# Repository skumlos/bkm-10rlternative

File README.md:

BKM-10Rlternative, a plug-and-play replacement for the BKM-10R/11R (except for memory card, for now).

Inspired by Aaron Bonhams BKM-10Rduino, which is genious!

Still early, and there's a LOT of components, plus some tweaks might still be needed: 
* Button RC-filters, as I feel that the 10nF should be replaced with 100nF, but needs testing.
* LED current limiting resistors is of course a preference. I used 470 Ohm in my first prototype.
* UART CTS/RTS pins are sorta irrelevant, as they're set static anyways. Removing these would also free
up pins for porting to regular Atmega328P/Arduino Nano 3.0 board.
* The discrete SS pins for each MCP23S17 should be irrelevant when using multiple addresses (which they
are configured as) so removing them in the future, to free up pins would be an idea.

Plans on memory card stuff for firmware updates and such via SD cards, is planned, at least to be researched.

While the unit is modeled after the BKM-11R, the wiring of the serial port is done like the BKM-10R, meaning
it uses a straight through male-male RS232/DE-9 cable, just like the BKM-10R. It is therefore not compatible
with BKM-11R DE-9 -> mini-DIN cables, unless you make your own.

There is a "classic" IR receiver designed into the PCB. It is unused at the moment, and shouldn't be mounted
before the software actually uses it. It was/is meant to be able to replicate some of the BKM-10Rduino 
functionality at some point, to have an all-in-one unit.

(2022) Martin Hejnfelt, martin@hejnfelt.com

https://www.immerhax.com

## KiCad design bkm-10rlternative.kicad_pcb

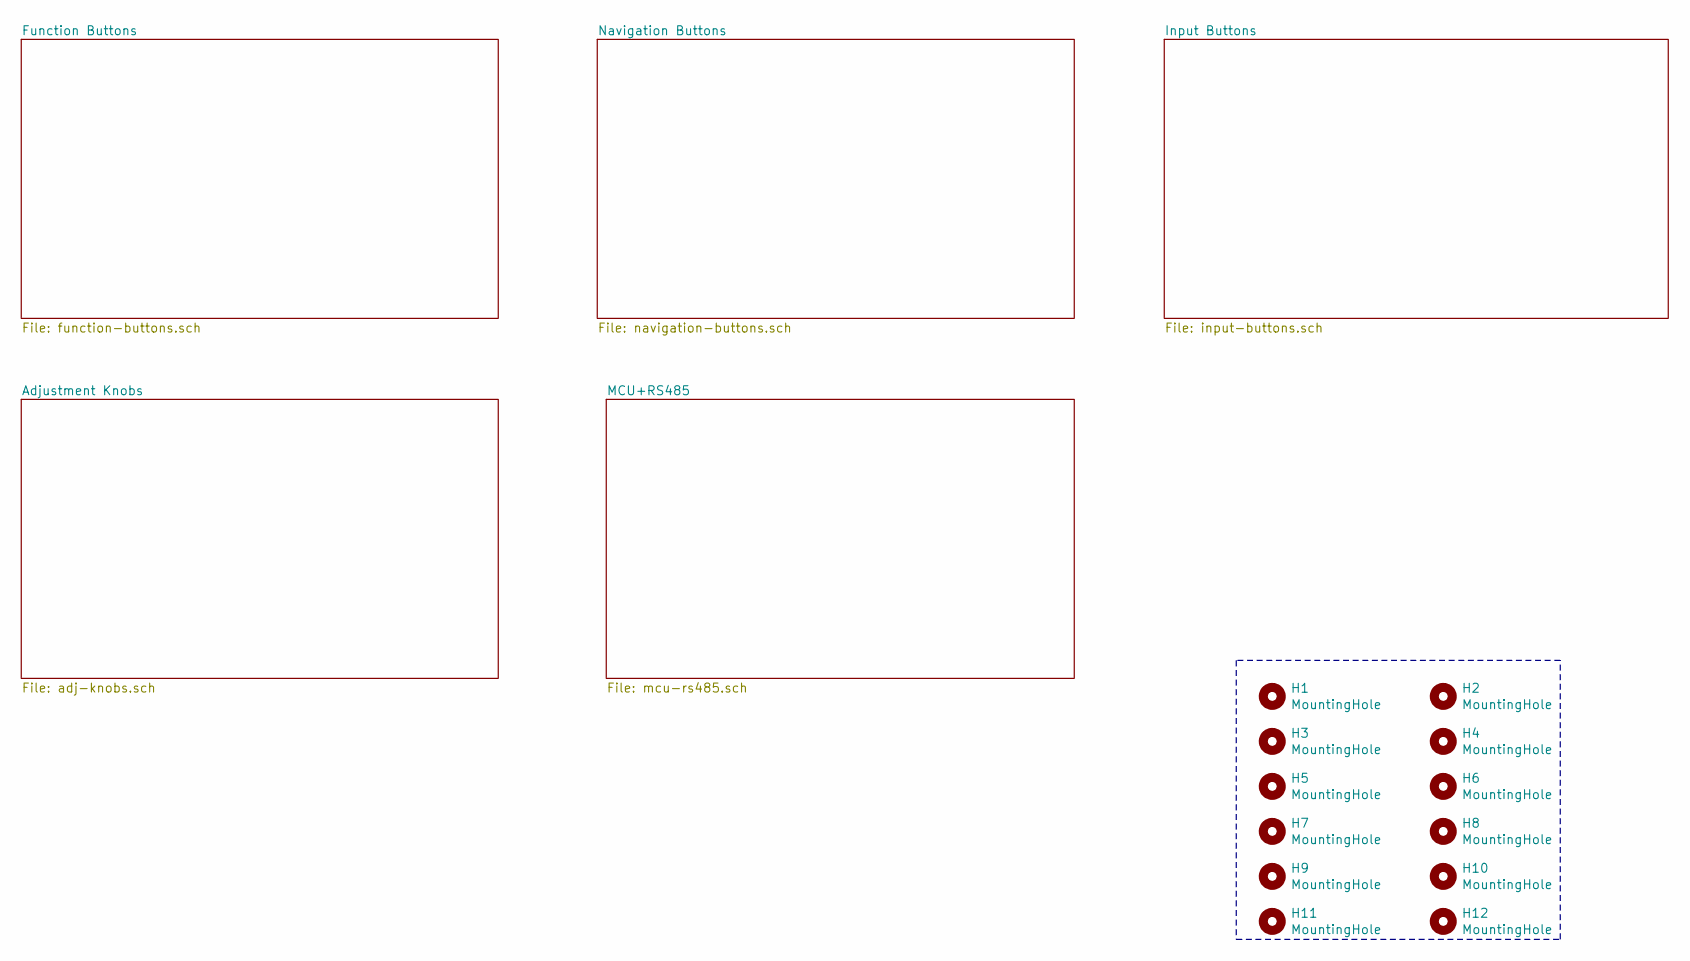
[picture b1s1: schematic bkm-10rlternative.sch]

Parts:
H1, H2, H3, H4, H5, H6, H7, H8, H9, H10, H11, H12: MountingHole; MountingHole_3.2mm_M3

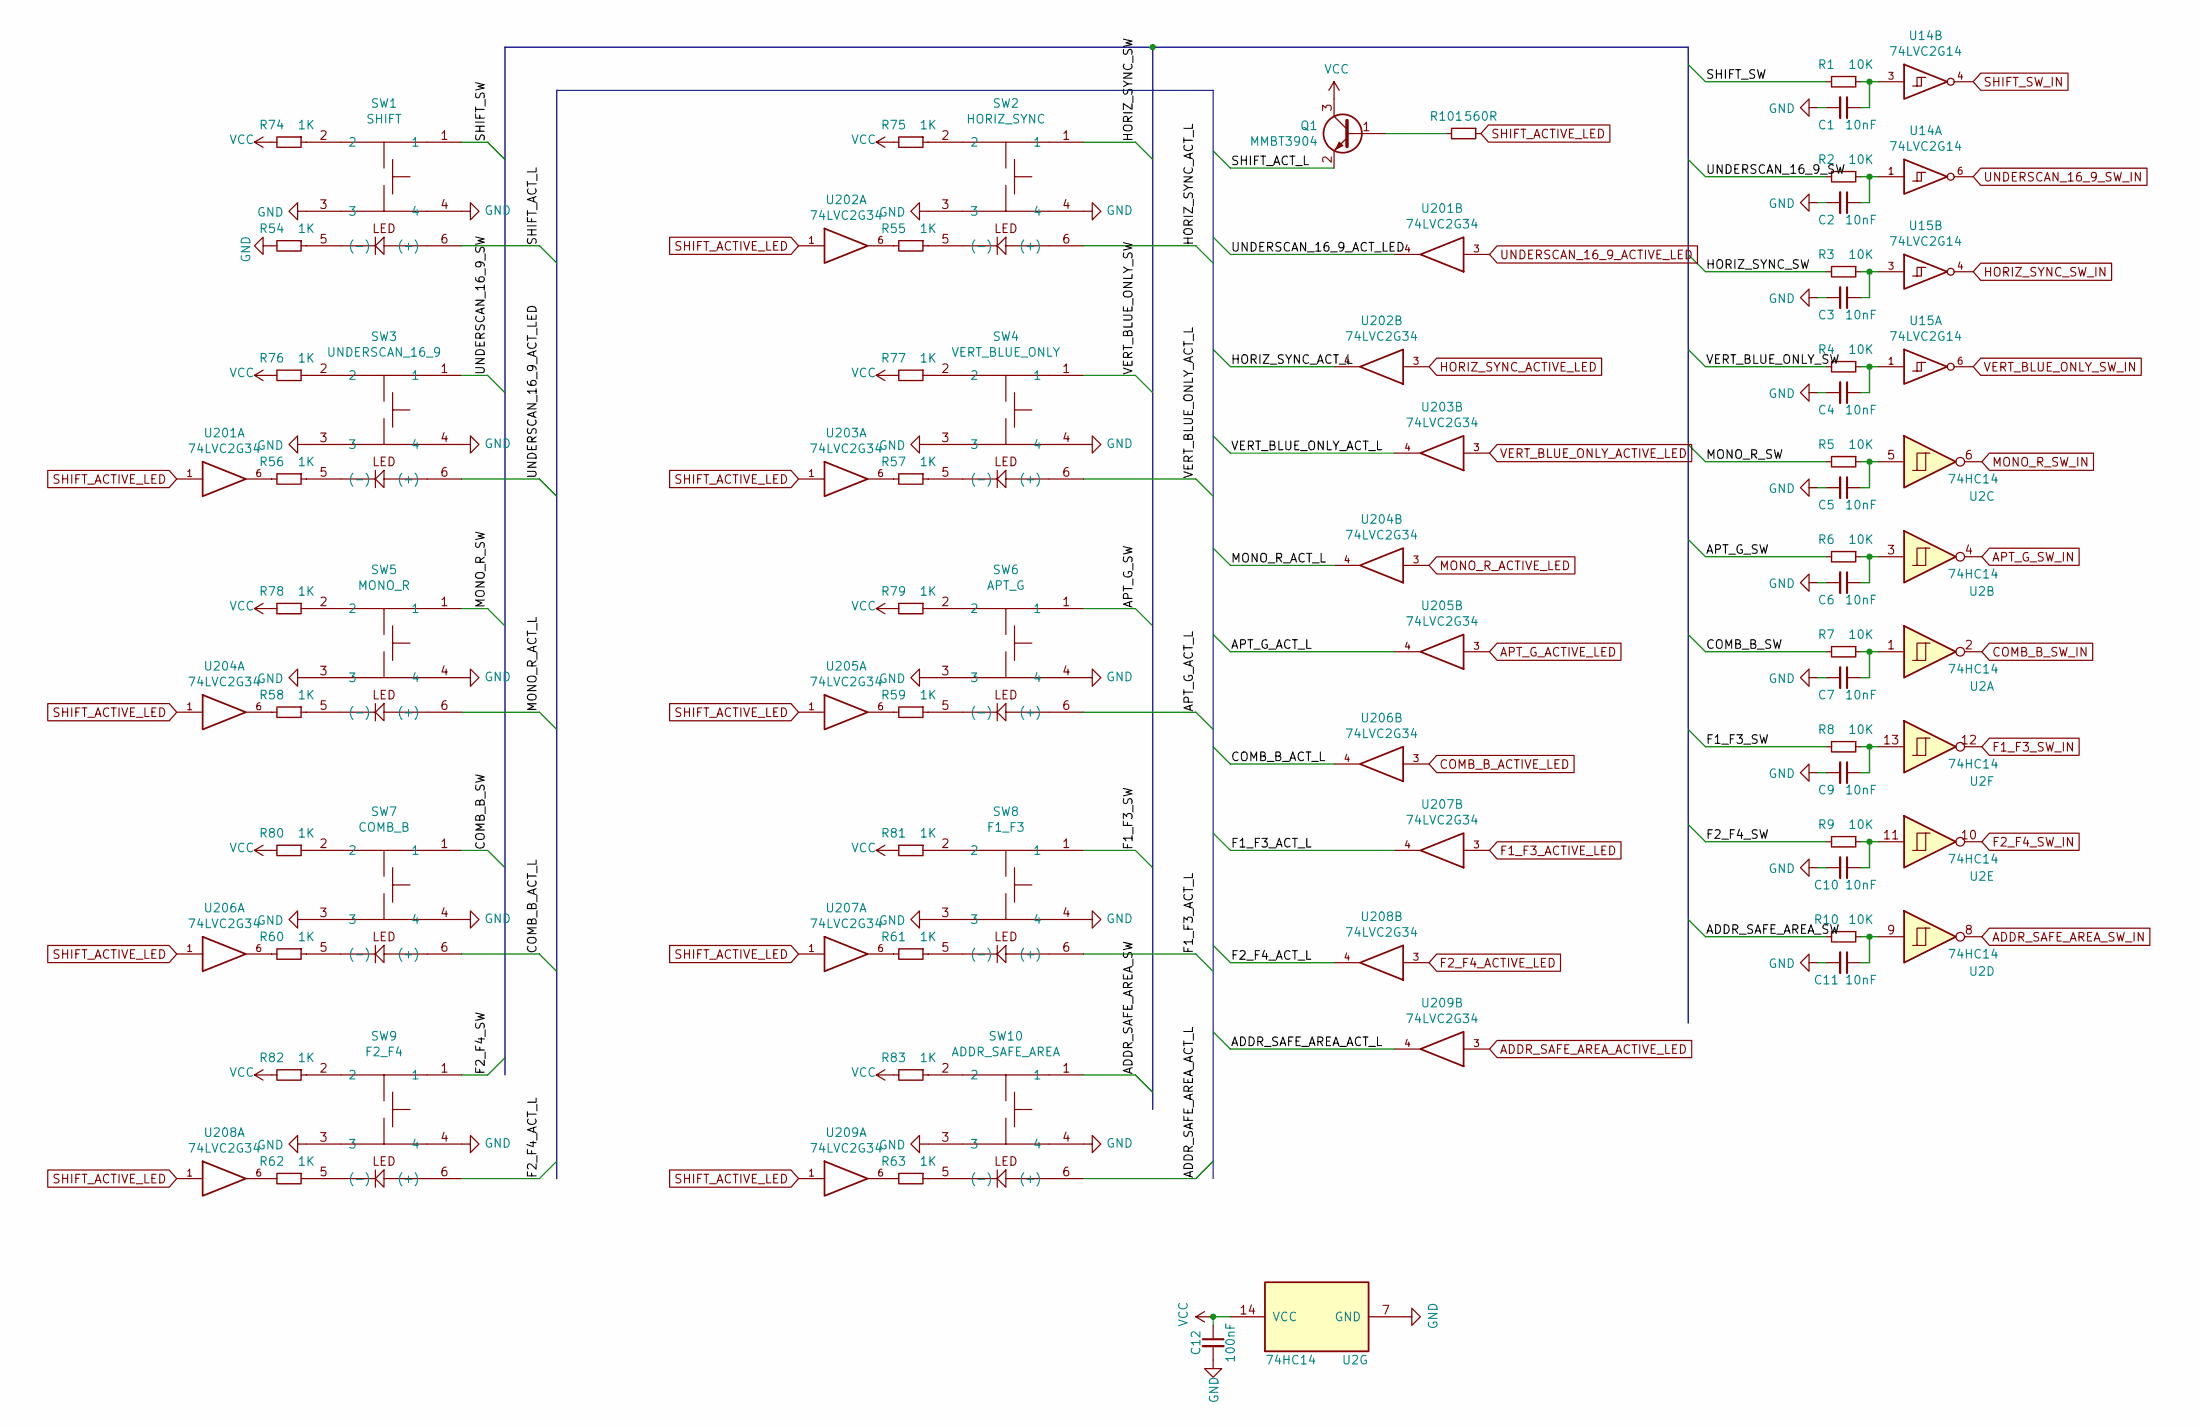
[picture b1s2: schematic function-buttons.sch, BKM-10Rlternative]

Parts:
C1, C2, C3, C4, C5, C6, C7, C9, C10, C11: 10nF; C_0603_1608Metric_Pad1.08x0.95mm_HandSolder
C12: 100nF; C_0603_1608Metric_Pad1.08x0.95mm_HandSolder
Q1: MMBT3904; SOT-23
R1, R2, R3, R4, R5, R6, R7, R8, R9, R10: 10K; R_0603_1608Metric_Pad0.98x0.95mm_HandSolder
R54, R55, R56, R57, R58, R59, R60, R61, R62, R63, R74, R75, R76, R77, R78, R79, R80, R81, R82, R83: 1K; R_0603_1608Metric_Pad0.98x0.95mm_HandSolder
R101: 560R; R_0603_1608Metric_Pad0.98x0.95mm_HandSolder
SW1: SHIFT; TL-1265
SW2: HORIZ_SYNC; TL-1265
SW3: UNDERSCAN_16_9; TL-1265
SW4: VERT_BLUE_ONLY; TL-1265
SW5: MONO_R; TL-1265
SW6: APT_G; TL-1265
SW7: COMB_B; TL-1265
SW8: F1_F3; TL-1265
SW9: F2_F4; TL-1265
SW10: ADDR_SAFE_AREA; TL-1265
U2: 74HC14; TSSOP-14_4.4x5mm_P0.65mm
U14, U15: 74LVC2G14; SOT-23-6_Handsoldering
U201, U202, U203, U204, U205, U206, U207, U208, U209: 74LVC2G34; SOT-23-6_Handsoldering

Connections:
/Function Buttons/ADDR_SAFE_AREA_ACT_L: SW10.6 ((+)), U209.4
/Function Buttons/ADDR_SAFE_AREA_SW: R10.2, SW10.1
/Function Buttons/APT_G_ACT_L: SW6.6 ((+)), U205.4
/Function Buttons/APT_G_SW: R6.2, SW6.1
/Function Buttons/COMB_B_ACT_L: SW7.6 ((+)), U206.4
/Function Buttons/COMB_B_SW: R7.2, SW7.1
/Function Buttons/F1_F3_ACT_L: SW8.6 ((+)), U207.4
/Function Buttons/F1_F3_SW: R8.2, SW8.1
/Function Buttons/F2_F4_ACT_L: SW9.6 ((+)), U208.4
/Function Buttons/F2_F4_SW: R9.2, SW9.1
/Function Buttons/HORIZ_SYNC_ACT_L: SW2.6 ((+)), U202.4
/Function Buttons/HORIZ_SYNC_SW: R3.2, SW2.1
/Function Buttons/MONO_R_ACT_L: SW5.6 ((+)), U204.4
/Function Buttons/MONO_R_SW: R5.2, SW5.1
/Function Buttons/SHIFT_ACT_L: Q1.2 (E), SW1.6 ((+))
/Function Buttons/SHIFT_SW: R1.2, SW1.1
/Function Buttons/UNDERSCAN_16_9_ACT_LED: SW3.6 ((+)), U201.4
/Function Buttons/UNDERSCAN_16_9_SW: R2.2, SW3.1
/Function Buttons/VERT_BLUE_ONLY_ACT_L: SW4.6 ((+)), U203.4
/Function Buttons/VERT_BLUE_ONLY_SW: R4.2, SW4.1
ADDR_SAFE_AREA_ACTIVE_LED: U209.3; also elsewhere on the board
ADDR_SAFE_AREA_SW_IN: U2.8; also elsewhere on the board
APT_G_ACTIVE_LED: U205.3; also elsewhere on the board
APT_G_SW_IN: U2.4; also elsewhere on the board
COMB_B_ACTIVE_LED: U206.3; also elsewhere on the board
COMB_B_SW_IN: U2.2; also elsewhere on the board
F1_F3_ACTIVE_LED: U207.3; also elsewhere on the board
F1_F3_SW_IN: U2.12; also elsewhere on the board
F2_F4_ACTIVE_LED: U208.3; also elsewhere on the board
F2_F4_SW_IN: U2.10; also elsewhere on the board
GND: C1.2, C2.2, C3.2, C4.2, C5.2, C6.2, C7.2, C9.2, C10.2, C11.2, C12.2, R54.2, SW1.3, SW1.4, SW2.3, SW2.4, SW3.3, SW3.4, SW4.3, SW4.4, SW5.3, SW5.4, SW6.3, SW6.4, SW7.3, SW7.4, SW8.3, SW8.4, SW9.3, SW9.4, SW10.3, SW10.4, U2.7 (GND), U14.2 (GND), U15.2 (GND), U201.2 (GND), U202.2 (GND), U203.2 (GND), U204.2 (GND), U205.2 (GND), U206.2 (GND), U207.2 (GND), U208.2 (GND), U209.2 (GND); also elsewhere on the board
HORIZ_SYNC_ACTIVE_LED: U202.3; also elsewhere on the board
HORIZ_SYNC_SW_IN: U15.4; also elsewhere on the board
MONO_R_ACTIVE_LED: U204.3; also elsewhere on the board
MONO_R_SW_IN: U2.6; also elsewhere on the board
unnamed: C1.1, R1.1, U14.3
unnamed: C2.1, R2.1, U14.1
unnamed: C3.1, R3.1, U15.3
unnamed: C4.1, R4.1, U15.1
unnamed: C5.1, R5.1, U2.5
unnamed: C6.1, R6.1, U2.3
unnamed: C7.1, R7.1, U2.1
unnamed: C9.1, R8.1, U2.13
unnamed: C10.1, R9.1, U2.11
unnamed: C11.1, R10.1, U2.9
unnamed: Q1.1 (B), R101.2
unnamed: R54.1, SW1.5 ((-))
unnamed: R55.1, SW2.5 ((-))
unnamed: R55.2, U202.6
unnamed: R56.1, SW3.5 ((-))
unnamed: R56.2, U201.6
unnamed: R57.1, SW4.5 ((-))
unnamed: R57.2, U203.6
unnamed: R58.1, SW5.5 ((-))
unnamed: R58.2, U204.6
unnamed: R59.1, SW6.5 ((-))
unnamed: R59.2, U205.6
unnamed: R60.1, SW7.5 ((-))
unnamed: R60.2, U206.6
unnamed: R61.1, SW8.5 ((-))
unnamed: R61.2, U207.6
unnamed: R62.1, SW9.5 ((-))
unnamed: R62.2, U208.6
unnamed: R63.1, SW10.5 ((-))
unnamed: R63.2, U209.6
unnamed: R74.1, SW1.2
unnamed: R75.1, SW2.2
unnamed: R76.1, SW3.2
unnamed: R77.1, SW4.2
unnamed: R78.1, SW5.2
unnamed: R79.1, SW6.2
unnamed: R80.1, SW7.2
unnamed: R81.1, SW8.2
unnamed: R82.1, SW9.2
unnamed: R83.1, SW10.2
SHIFT_ACTIVE_LED: R101.1, U201.1, U202.1, U203.1, U204.1, U205.1, U206.1, U207.1, U208.1, U209.1; also elsewhere on the board
SHIFT_SW_IN: U14.4; also elsewhere on the board
UNDERSCAN_16_9_ACTIVE_LED: U201.3; also elsewhere on the board
UNDERSCAN_16_9_SW_IN: U14.6; also elsewhere on the board
VCC: C12.1, Q1.3 (C), R74.2, R75.2, R76.2, R77.2, R78.2, R79.2, R80.2, R81.2, R82.2, R83.2, U2.14 (VCC), U14.5 (VCC), U15.5 (VCC), U201.5 (VCC), U202.5 (VCC), U203.5 (VCC), U204.5 (VCC), U205.5 (VCC), U206.5 (VCC), U207.5 (VCC), U208.5 (VCC), U209.5 (VCC); also elsewhere on the board
VERT_BLUE_ONLY_ACTIVE_LED: U203.3; also elsewhere on the board
VERT_BLUE_ONLY_SW_IN: U15.6; also elsewhere on the board

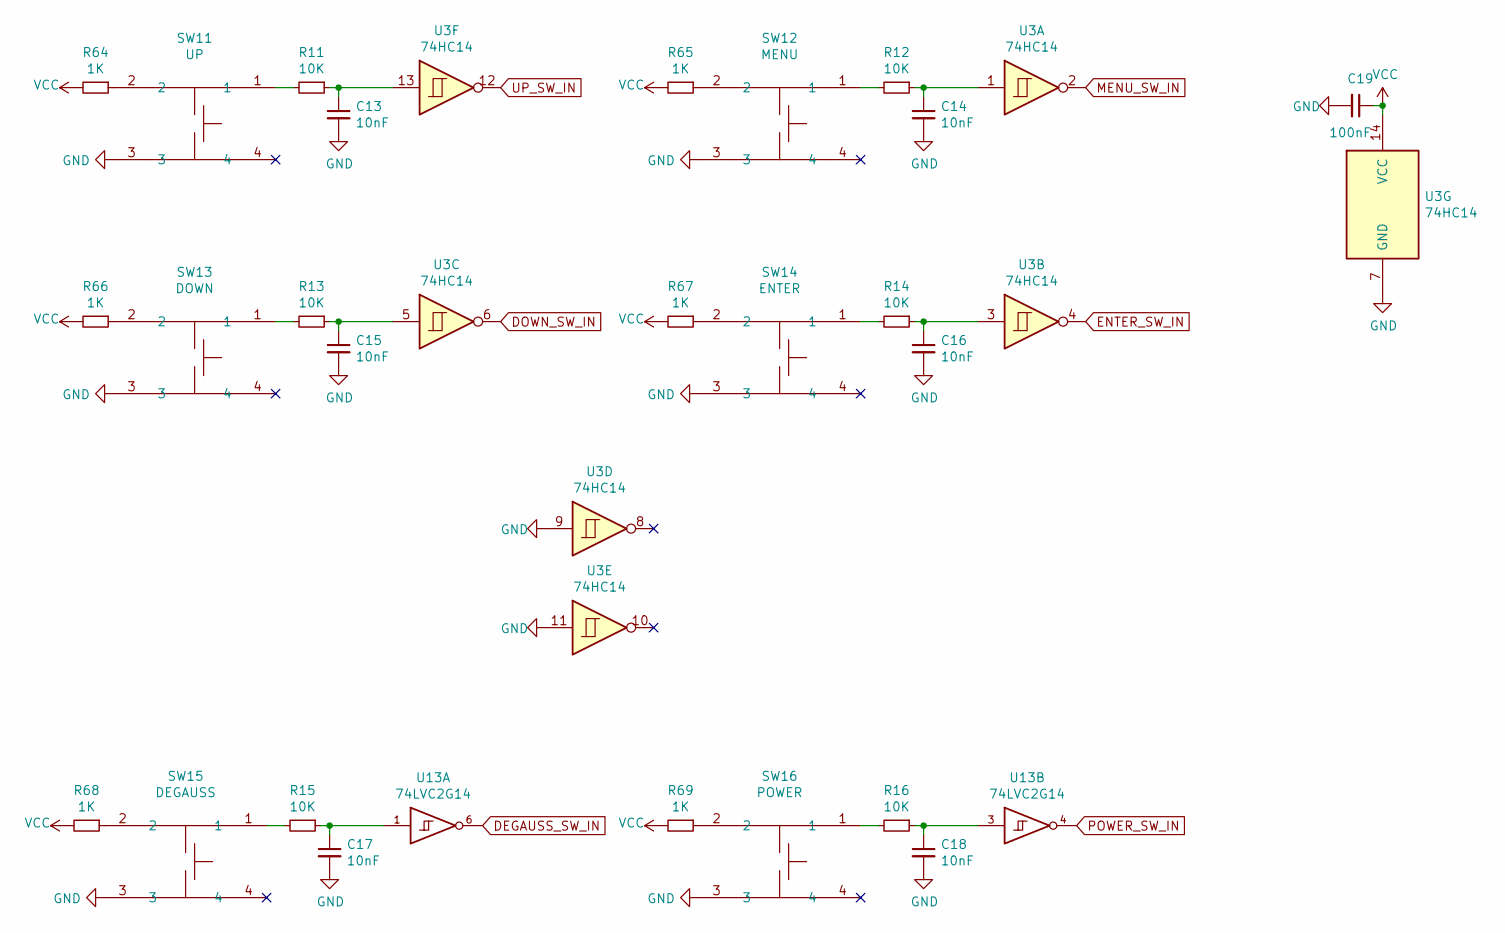
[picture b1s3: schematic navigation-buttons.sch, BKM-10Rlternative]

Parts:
C13, C14, C15, C16, C17, C18: 10nF; C_0603_1608Metric_Pad1.08x0.95mm_HandSolder
C19: 100nF; C_0603_1608Metric_Pad1.08x0.95mm_HandSolder
R11, R12, R13, R14, R15, R16: 10K; R_0603_1608Metric_Pad0.98x0.95mm_HandSolder
R64, R65, R66, R67, R68, R69: 1K; R_0603_1608Metric_Pad0.98x0.95mm_HandSolder
SW11: UP; TL-1265_NO_LED
SW12: MENU; TL-1265_NO_LED
SW13: DOWN; TL-1265_NO_LED
SW14: ENTER; TL-1265_NO_LED
SW15: DEGAUSS; TL-1265_NO_LED
SW16: POWER; TL-1265_NO_LED
U3: 74HC14; TSSOP-14_4.4x5mm_P0.65mm
U13: 74LVC2G14; SOT-23-6_Handsoldering

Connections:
DEGAUSS_SW_IN: U13.6; also elsewhere on the board
DOWN_SW_IN: U3.6; also elsewhere on the board
ENTER_SW_IN: U3.4; also elsewhere on the board
GND: C13.2, C14.2, C15.2, C16.2, C17.2, C18.2, C19.2, SW11.3, SW12.3, SW13.3, SW14.3, SW15.3, SW16.3, U3.7 (GND), U3.9, U3.11, U13.2 (GND); also elsewhere on the board
MENU_SW_IN: U3.2; also elsewhere on the board
unnamed: C13.1, R11.1, U3.13
unnamed: C14.1, R12.1, U3.1
unnamed: C15.1, R13.1, U3.5
unnamed: C16.1, R14.1, U3.3
unnamed: C17.1, R15.1, U13.1
unnamed: C18.1, R16.1, U13.3
unnamed: R11.2, SW11.1
unnamed: R12.2, SW12.1
unnamed: R13.2, SW13.1
unnamed: R14.2, SW14.1
unnamed: R15.2, SW15.1
unnamed: R16.2, SW16.1
unnamed: R64.1, SW11.2
unnamed: R65.1, SW12.2
unnamed: R66.1, SW13.2
unnamed: R67.1, SW14.2
unnamed: R68.1, SW15.2
unnamed: R69.1, SW16.2
POWER_SW_IN: U13.4; also elsewhere on the board
UP_SW_IN: U3.12; also elsewhere on the board
VCC: C19.1, R64.2, R65.2, R66.2, R67.2, R68.2, R69.2, U3.14 (VCC), U13.5 (VCC); also elsewhere on the board

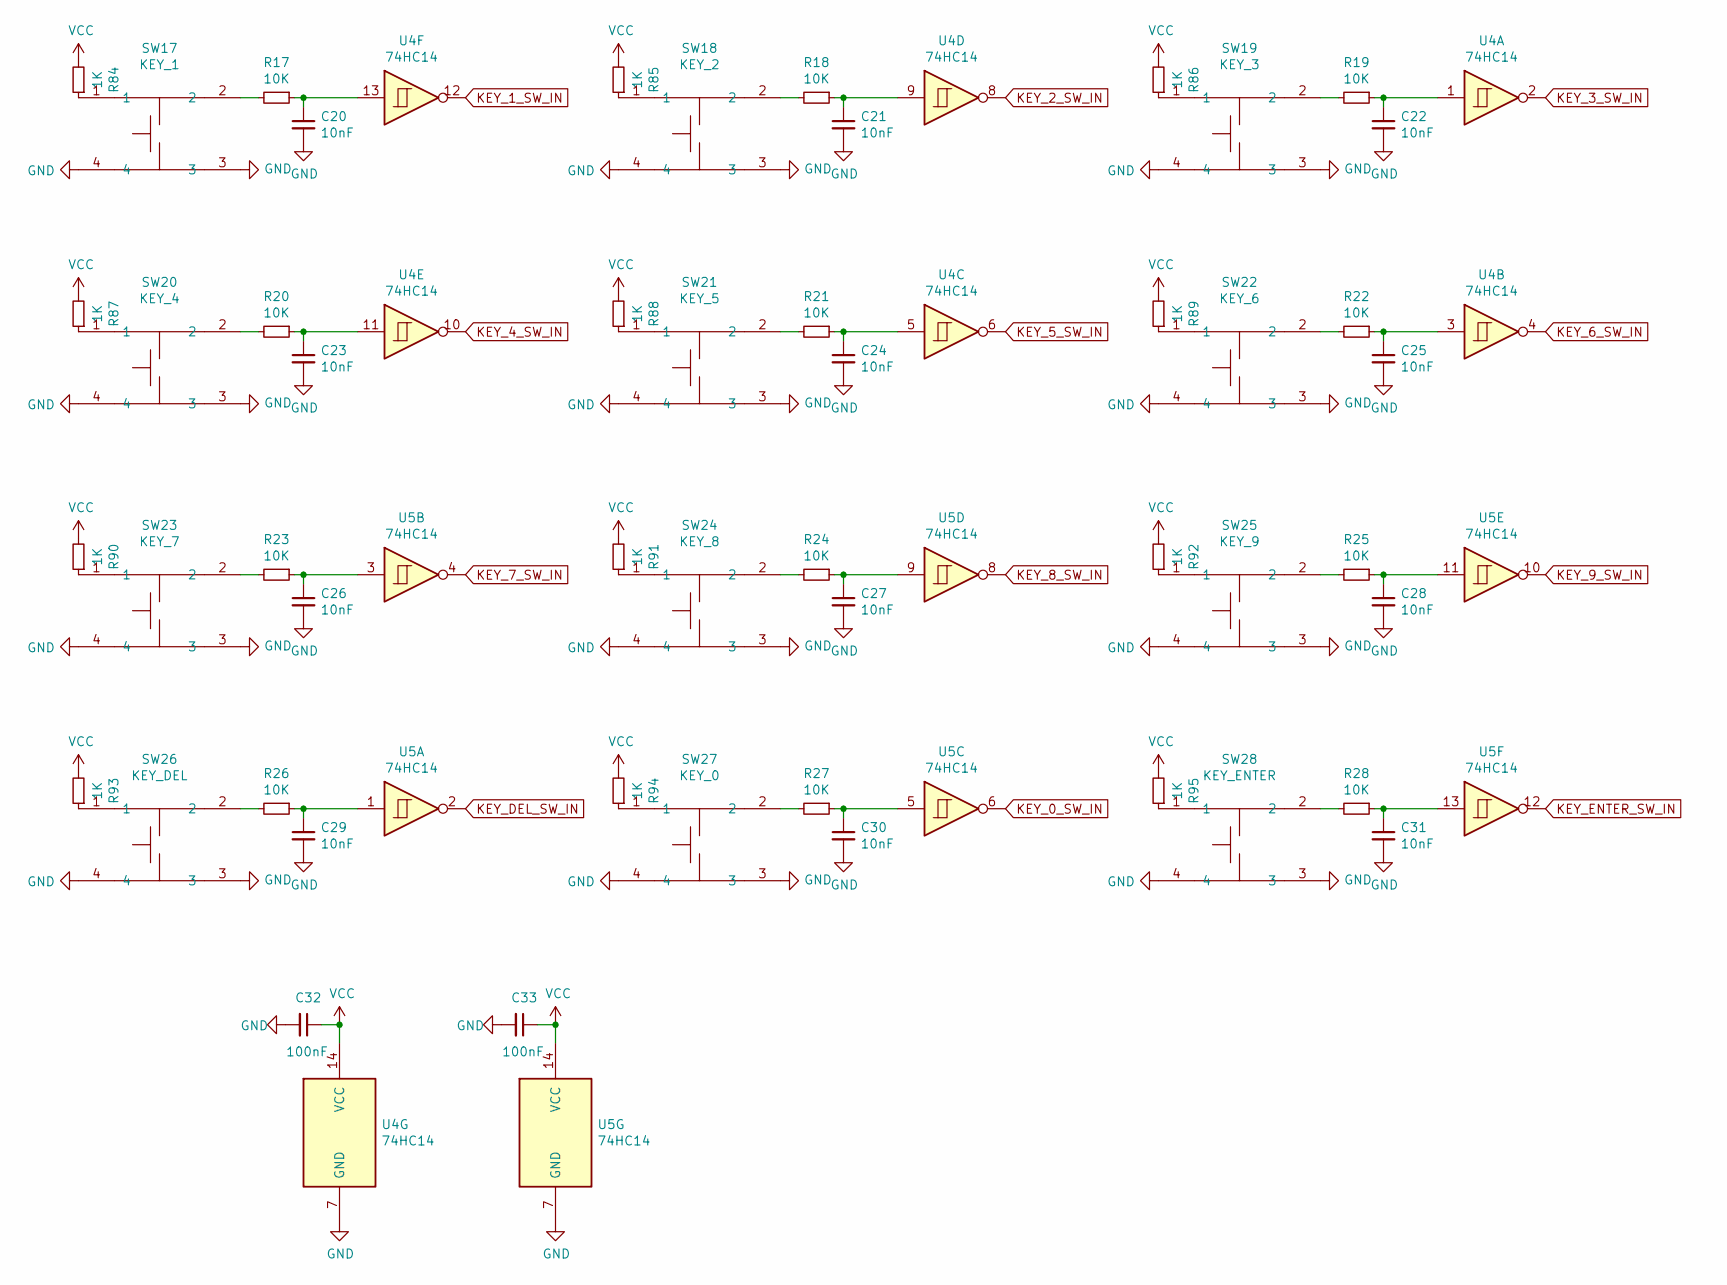
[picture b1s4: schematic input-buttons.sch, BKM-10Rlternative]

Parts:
C20, C21, C22, C23, C24, C25, C26, C27, C28, C29, C30, C31: 10nF; C_0603_1608Metric_Pad1.08x0.95mm_HandSolder
C32, C33: 100nF; C_0603_1608Metric_Pad1.08x0.95mm_HandSolder
R17, R18, R19, R20, R21, R22, R23, R24, R25, R26, R27, R28: 10K; R_0603_1608Metric_Pad0.98x0.95mm_HandSolder
R84, R85, R86, R87, R88, R89, R90, R91, R92, R93, R94, R95: 1K; R_0603_1608Metric_Pad0.98x0.95mm_HandSolder
SW17: KEY_1; TL-1265_NO_LED
SW18: KEY_2; TL-1265_NO_LED
SW19: KEY_3; TL-1265_NO_LED
SW20: KEY_4; TL-1265_NO_LED
SW21: KEY_5; TL-1265_NO_LED
SW22: KEY_6; TL-1265_NO_LED
SW23: KEY_7; TL-1265_NO_LED
SW24: KEY_8; TL-1265_NO_LED
SW25: KEY_9; TL-1265_NO_LED
SW26: KEY_DEL; TL-1265_NO_LED
SW27: KEY_0; TL-1265_NO_LED
SW28: KEY_ENTER; TL-1265_NO_LED
U4, U5: 74HC14; TSSOP-14_4.4x5mm_P0.65mm

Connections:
GND: C20.2, C21.2, C22.2, C23.2, C24.2, C25.2, C26.2, C27.2, C28.2, C29.2, C30.2, C31.2, C32.2, C33.2, SW17.3, SW17.4, SW18.3, SW18.4, SW19.3, SW19.4, SW20.3, SW20.4, SW21.3, SW21.4, SW22.3, SW22.4, SW23.3, SW23.4, SW24.3, SW24.4, SW25.3, SW25.4, SW26.3, SW26.4, SW27.3, SW27.4, SW28.3, SW28.4, U4.7 (GND), U5.7 (GND); also elsewhere on the board
KEY_0_SW_IN: U5.6; also elsewhere on the board
KEY_1_SW_IN: U4.12; also elsewhere on the board
KEY_2_SW_IN: U4.8; also elsewhere on the board
KEY_3_SW_IN: U4.2; also elsewhere on the board
KEY_4_SW_IN: U4.10; also elsewhere on the board
KEY_5_SW_IN: U4.6; also elsewhere on the board
KEY_6_SW_IN: U4.4; also elsewhere on the board
KEY_7_SW_IN: U5.4; also elsewhere on the board
KEY_8_SW_IN: U5.8; also elsewhere on the board
KEY_9_SW_IN: U5.10; also elsewhere on the board
KEY_DEL_SW_IN: U5.2; also elsewhere on the board
KEY_ENTER_SW_IN: U5.12; also elsewhere on the board
unnamed: C20.1, R17.1, U4.13
unnamed: C21.1, R18.1, U4.9
unnamed: C22.1, R19.1, U4.1
unnamed: C23.1, R20.1, U4.11
unnamed: C24.1, R21.1, U4.5
unnamed: C25.1, R22.1, U4.3
unnamed: C26.1, R23.1, U5.3
unnamed: C27.1, R24.1, U5.9
unnamed: C28.1, R25.1, U5.11
unnamed: C29.1, R26.1, U5.1
unnamed: C30.1, R27.1, U5.5
unnamed: C31.1, R28.1, U5.13
unnamed: R17.2, SW17.2
unnamed: R18.2, SW18.2
unnamed: R19.2, SW19.2
unnamed: R20.2, SW20.2
unnamed: R21.2, SW21.2
unnamed: R22.2, SW22.2
unnamed: R23.2, SW23.2
unnamed: R24.2, SW24.2
unnamed: R25.2, SW25.2
unnamed: R26.2, SW26.2
unnamed: R27.2, SW27.2
unnamed: R28.2, SW28.2
unnamed: R84.1, SW17.1
unnamed: R85.1, SW18.1
unnamed: R86.1, SW19.1
unnamed: R87.1, SW20.1
unnamed: R88.1, SW21.1
unnamed: R89.1, SW22.1
unnamed: R90.1, SW23.1
unnamed: R91.1, SW24.1
unnamed: R92.1, SW25.1
unnamed: R93.1, SW26.1
unnamed: R94.1, SW27.1
unnamed: R95.1, SW28.1
VCC: C32.1, C33.1, R84.2, R85.2, R86.2, R87.2, R88.2, R89.2, R90.2, R91.2, R92.2, R93.2, R94.2, R95.2, U4.14 (VCC), U5.14 (VCC); also elsewhere on the board

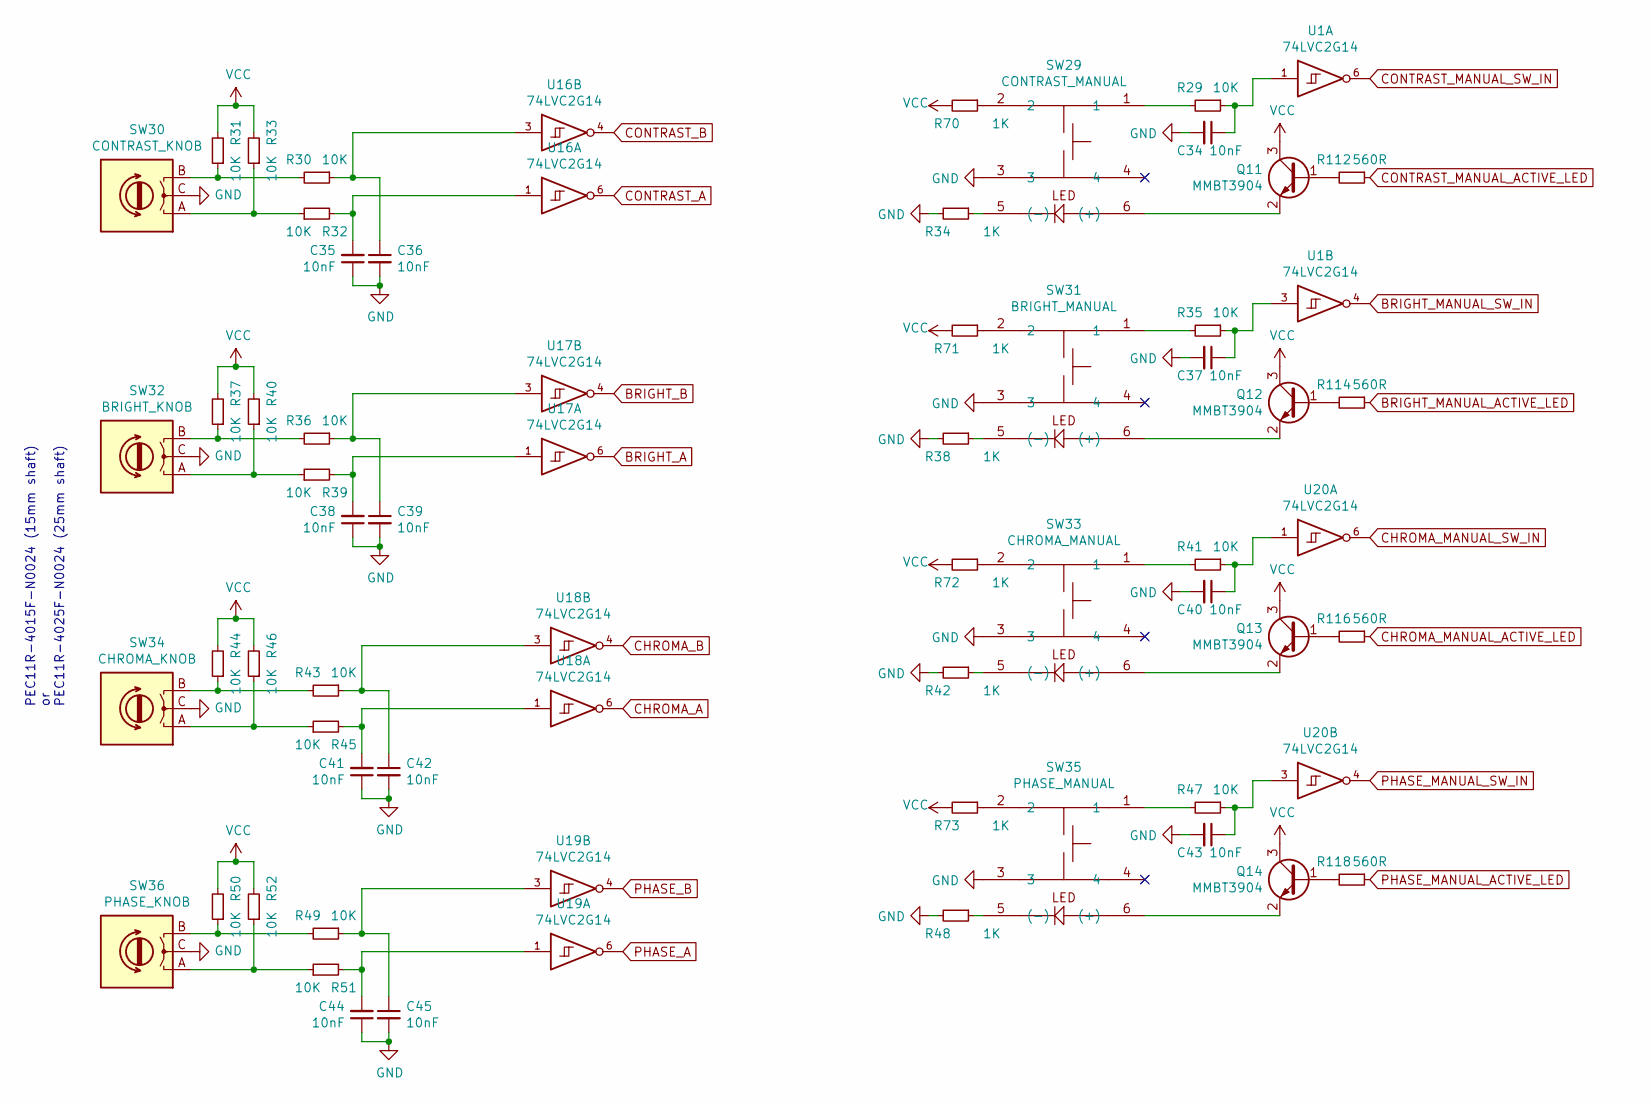
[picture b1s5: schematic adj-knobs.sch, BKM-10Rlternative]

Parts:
C34, C35, C36, C37, C38, C39, C40, C41, C42, C43, C44, C45: 10nF; C_0603_1608Metric_Pad1.08x0.95mm_HandSolder
Q11, Q12, Q13, Q14: MMBT3904; SOT-23
R29, R30, R31, R32, R33, R35, R36, R37, R39, R40, R41, R43, R44, R45, R46, R47, R49, R50, R51, R52: 10K; R_0603_1608Metric_Pad0.98x0.95mm_HandSolder
R34, R38, R42, R48, R70, R71, R72, R73: 1K; R_0603_1608Metric_Pad0.98x0.95mm_HandSolder
R112, R114, R116, R118: 560R; R_0603_1608Metric_Pad0.98x0.95mm_HandSolder
SW29: CONTRAST_MANUAL; TL-1265
SW30: CONTRAST_KNOB; RotaryEncoder_Alps_EC11E_Vertical_H20mm
SW31: BRIGHT_MANUAL; TL-1265
SW32: BRIGHT_KNOB; RotaryEncoder_Alps_EC11E_Vertical_H20mm
SW33: CHROMA_MANUAL; TL-1265
SW34: CHROMA_KNOB; RotaryEncoder_Alps_EC11E_Vertical_H20mm
SW35: PHASE_MANUAL; TL-1265
SW36: PHASE_KNOB; RotaryEncoder_Alps_EC11E_Vertical_H20mm
U1, U16, U17, U18, U19, U20: 74LVC2G14; SOT-23-6_Handsoldering

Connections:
BRIGHT_A: U17.6; also elsewhere on the board
BRIGHT_B: U17.4; also elsewhere on the board
BRIGHT_MANUAL_ACTIVE_LED: R114.1; also elsewhere on the board
BRIGHT_MANUAL_SW_IN: U1.4; also elsewhere on the board
CHROMA_A: U18.6; also elsewhere on the board
CHROMA_B: U18.4; also elsewhere on the board
CHROMA_MANUAL_ACTIVE_LED: R116.1; also elsewhere on the board
CHROMA_MANUAL_SW_IN: U20.6; also elsewhere on the board
CONTRAST_A: U16.6; also elsewhere on the board
CONTRAST_B: U16.4; also elsewhere on the board
CONTRAST_MANUAL_ACTIVE_LED: R112.1; also elsewhere on the board
CONTRAST_MANUAL_SW_IN: U1.6; also elsewhere on the board
GND: C34.2, C35.1, C36.2, C37.2, C38.1, C39.2, C40.2, C41.1, C42.2, C43.2, C44.1, C45.2, R34.2, R38.2, R42.2, R48.2, SW29.3, SW30.C, SW31.3, SW32.C, SW33.3, SW34.C, SW35.3, SW36.C, U1.2 (GND), U16.2 (GND), U17.2 (GND), U18.2 (GND), U19.2 (GND), U20.2 (GND); also elsewhere on the board
unnamed: C34.1, R29.1, U1.1
unnamed: C35.2, R32.2, U16.1
unnamed: C36.1, R30.1, U16.3
unnamed: C37.1, R35.1, U1.3
unnamed: C38.2, R39.2, U17.1
unnamed: C39.1, R36.1, U17.3
unnamed: C40.1, R41.1, U20.1
unnamed: C41.2, R45.2, U18.1
unnamed: C42.1, R43.1, U18.3
unnamed: C43.1, R47.1, U20.3
unnamed: C44.2, R51.2, U19.1
unnamed: C45.1, R49.1, U19.3
unnamed: Q11.1 (B), R112.2
unnamed: Q11.2 (E), SW29.6 ((+))
unnamed: Q12.1 (B), R114.2
unnamed: Q12.2 (E), SW31.6 ((+))
unnamed: Q13.1 (B), R116.2
unnamed: Q13.2 (E), SW33.6 ((+))
unnamed: Q14.1 (B), R118.2
unnamed: Q14.2 (E), SW35.6 ((+))
unnamed: R29.2, SW29.1
unnamed: R30.2, R31.1, SW30.B
unnamed: R32.1, R33.1, SW30.A
unnamed: R34.1, SW29.5 ((-))
unnamed: R35.2, SW31.1
unnamed: R36.2, R37.1, SW32.B
unnamed: R38.1, SW31.5 ((-))
unnamed: R39.1, R40.1, SW32.A
unnamed: R41.2, SW33.1
unnamed: R42.1, SW33.5 ((-))
unnamed: R43.2, R44.1, SW34.B
unnamed: R45.1, R46.1, SW34.A
unnamed: R47.2, SW35.1
unnamed: R48.1, SW35.5 ((-))
unnamed: R49.2, R50.1, SW36.B
unnamed: R51.1, R52.1, SW36.A
unnamed: R70.1, SW29.2
unnamed: R71.1, SW31.2
unnamed: R72.1, SW33.2
unnamed: R73.1, SW35.2
PHASE_A: U19.6; also elsewhere on the board
PHASE_B: U19.4; also elsewhere on the board
PHASE_MANUAL_ACTIVE_LED: R118.1; also elsewhere on the board
PHASE_MANUAL_SW_IN: U20.4; also elsewhere on the board
VCC: Q11.3 (C), Q12.3 (C), Q13.3 (C), Q14.3 (C), R31.2, R33.2, R37.2, R40.2, R44.2, R46.2, R50.2, R52.2, R70.2, R71.2, R72.2, R73.2, U1.5 (VCC), U16.5 (VCC), U17.5 (VCC), U18.5 (VCC), U19.5 (VCC), U20.5 (VCC); also elsewhere on the board

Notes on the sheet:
PEC11R-4015F-N0024 (15mm shaft) or PEC11R-4025F-N0024 (25mm shaft)
